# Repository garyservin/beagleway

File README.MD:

beagleway
=========

Plataforma robótica móvil basada en el principio del péndulo invertido utilizando una BeagleBone Black y un microcontrolador Mbed

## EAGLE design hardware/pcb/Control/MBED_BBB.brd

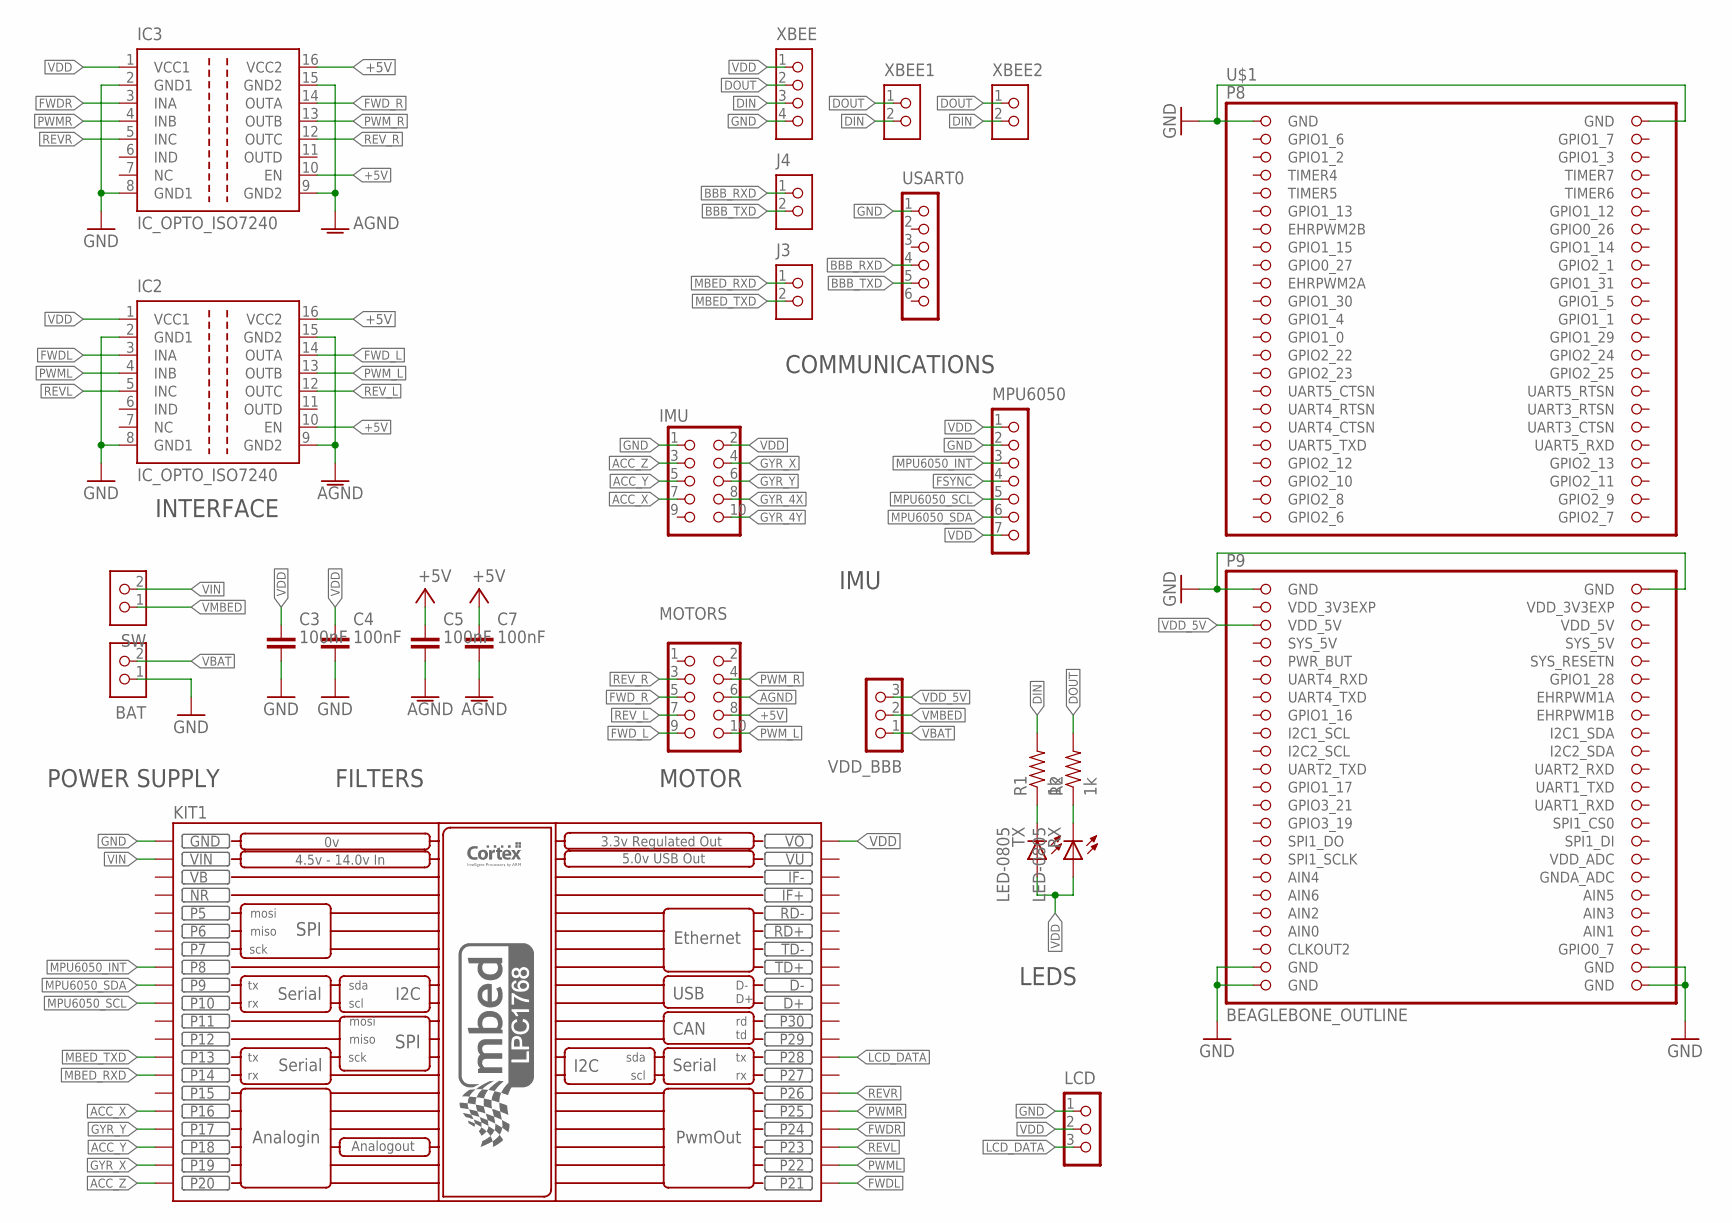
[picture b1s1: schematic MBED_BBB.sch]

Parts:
BAT: CON_HEADER_1X02-PTH-M; M1X02_M
C3, C4, C5, C7: 100nF; C0603
IC2, IC3: IC_OPTO_ISO7240; SOIC-16DW
IMU: CON_HEADER_2X05-PTH+SHROUDED_A; PINSHRD_PTH_2X05
J3, J4: CON_HEADER_1X02-PTH-M; M1X02_M
KIT1: MBED-SOCKET
LCD: CON_HEADER_1X03-PTH_M; M1X03_M
MOTORS: CON_HEADER_2X05-PTH+SHROUDED_A; PINSHRD_PTH_2X05
MPU6050: CON_HEADER_1X07-PTH_M; M1X07_M
R1, R2: 1k; R0603
RX: LED-0805
SW: CON_HEADER_1X02-PTH-POLAR; M1X02_P
TX: LED-0805
U$1: BEAGLEBONE_OUTLINE; BEAGLEBONE_SHIELD
USART0: CON_HEADER_1X06-PTH_M; M1X06_M
VDD_BBB: CON_HEADER_1X03-PTH_M; M1X03_M
XBEE: CON_HEADER_1X04-PTH_M; M1X04_M
XBEE1, XBEE2: CON_HEADER_1X02-PTH-M; M1X02_M

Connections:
+5V: C5.1, C7.1, IC2.10 (EN), IC2.16 (VCC2), IC3.10 (EN), IC3.16 (VCC2), MOTORS.8
ACC_X: IMU.7, KIT1.P16
ACC_Y: IMU.5, KIT1.P18
ACC_Z: IMU.3, KIT1.P20
AGND: C5.2, C7.2, IC2.9 (GND2), IC2.15 (GND2), IC3.9 (GND2), IC3.15 (GND2), MOTORS.6
AIN0: U$1.85 (AIN0)
BBB_RXD: J4.1, USART0.4
BBB_TXD: J4.2, USART0.5
DIN: R1.2, XBEE.3, XBEE1.2, XBEE2.2
DOUT: R2.2, XBEE.2, XBEE1.1, XBEE2.1
FSYNC: MPU6050.4
FWDL: IC2.3 (INA), KIT1.P21
FWDR: IC3.3 (INA), KIT1.P24
FWD_L: IC2.14 (OUTA), MOTORS.9
FWD_R: IC3.14 (OUTA), MOTORS.5
GND: BAT.1, C3.2, C4.2, IC2.2 (GND1), IC2.8 (GND1), IC3.2 (GND1), IC3.8 (GND1), IMU.1, KIT1.GND, LCD.1, MPU6050.2, U$1.1 (GND), U$1.2 (GND), U$1.47 (GND), U$1.48 (GND), U$1.89 (GND), U$1.90 (GND), U$1.91 (GND), U$1.92 (GND), USART0.1, XBEE.4
GYR_4X: IMU.8
GYR_4Y: IMU.10
GYR_X: IMU.4, KIT1.P19
GYR_Y: IMU.6, KIT1.P17
LCD_DATA: KIT1.P28, LCD.3
MBED_RXD: J3.1, KIT1.P14
MBED_TXD: J3.2, KIT1.P13
MPU6050_INT: KIT1.P8, MPU6050.3
MPU6050_SCL: KIT1.P10, MPU6050.5
MPU6050_SDA: KIT1.P9, MPU6050.6
NR: KIT1.NR
PWML: IC2.4 (INB), KIT1.P22
PWMR: IC3.4 (INB), KIT1.P25
PWM_L: IC2.13 (OUTB), MOTORS.10
PWM_R: IC3.13 (OUTB), MOTORS.4
REVL: IC2.5 (INC), KIT1.P23
REVR: IC3.5 (INC), KIT1.P26
REV_L: IC2.12 (OUTC), MOTORS.7
REV_R: IC3.12 (OUTC), MOTORS.3
RX_LED: R2.1, RX.C
SYS_5V: U$1.53 (SYS_5V)
TX_LED: R1.1, TX.C
VB: KIT1.VB
VBAT: BAT.2, VDD_BBB.1
VDD: C3.1, C4.1, IC2.1 (VCC1), IC3.1 (VCC1), IMU.2, KIT1.VOUT (VO), LCD.2, MPU6050.1, MPU6050.7, RX.A, TX.A, XBEE.1
VDD_3V3EXP: U$1.49 (VDD_3V3EXP), U$1.50 (VDD_3V3EXP)
VDD_5V: U$1.51 (VDD_5V), U$1.52 (VDD_5V), VDD_BBB.3
VIN: KIT1.VIN, SW.2
VMBED: SW.1, VDD_BBB.2
VU: KIT1.VU

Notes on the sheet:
POWER SUPPLY
COMMUNICATIONS
INTERFACE
FILTERS
LEDS
IMU
MOTOR

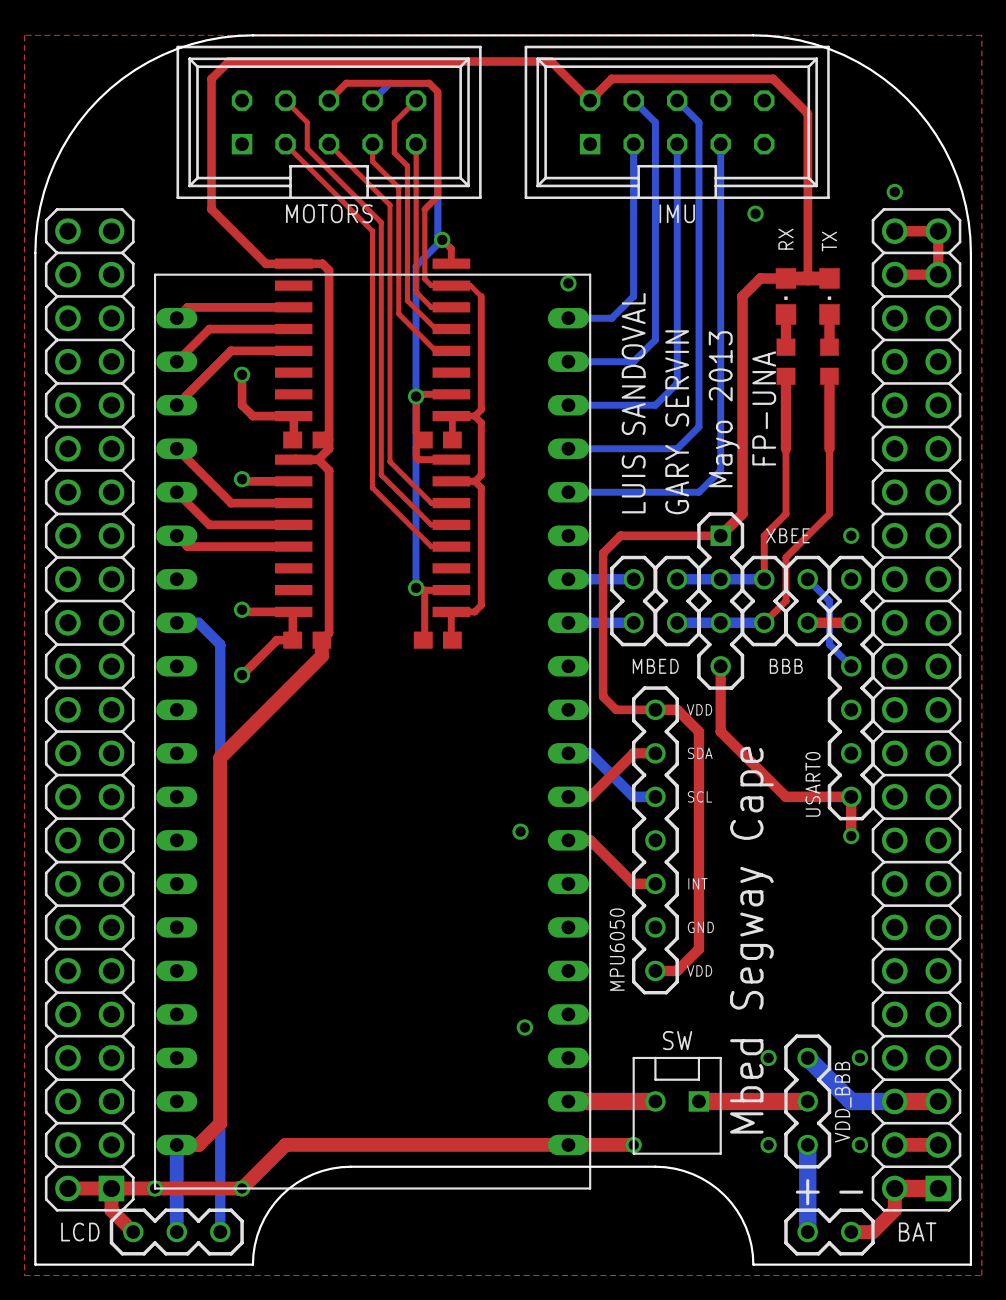
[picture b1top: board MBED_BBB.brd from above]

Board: 2 copper layers, 54.6 x 71.8 mm, 25 parts (0 on the bottom side), 38 nets.

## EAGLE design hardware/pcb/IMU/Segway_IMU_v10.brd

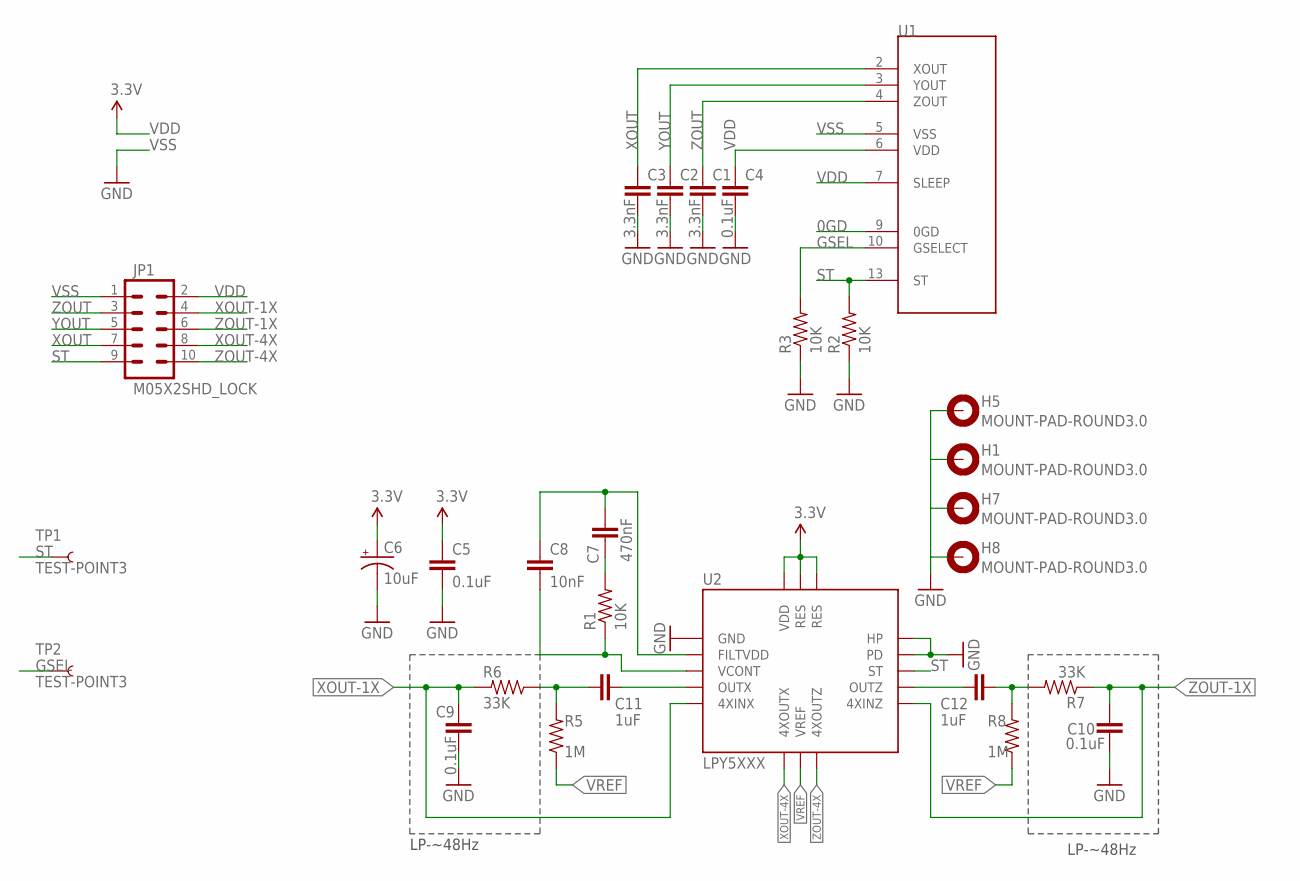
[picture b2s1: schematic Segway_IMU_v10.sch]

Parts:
C1, C2, C3: 3.3nF; 0402-CAP
C4, C5, C9, C10: 0.1uF; 0402-CAP
C6: 10uF; EIA3216
C7: 470nF; 0402-CAP
C8: 10nF; 0402-CAP
C11, C12: 1uF; 0402
H1, H5, H7, H8: MOUNT-PAD-ROUND3.0; 3,0-PAD
JP1: M05X2SHD_LOCK; 2X5-SHROUDED_LOCK
R1, R2, R3: 10K; 0402-RES
R5, R8: 1M; 0402-RES
R6, R7: 33K; 0402-RES
TP1, TP2: TEST-POINT3; PAD.03X.03
U1: MMA7361; LGA14
U2: LPY5XXX; ST-GYRO

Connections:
0GD: U1.9 (0GD)
F1: C7.1, C8.1, U2.2 (FILTVDD)
F2: C8.2, R1.1, U2.3 (VCONT)
GSEL: R3.2, TP2.P$1, U1.10 (GSELECT)
unnamed: C11.2, U2.4 (OUTX)
unnamed: C11.1, R5.2, R6.1
unnamed: C7.2, R1.2
unnamed: C12.1, U2.10 (OUTZ)
unnamed: C12.2, R7.2, R8.2
ST: JP1.9, R2.2, TP1.P$1, U1.13 (ST), U2.11 (ST)
VDD: C4.1, C5.1, C6.A (+), JP1.2, U1.6 (VDD), U1.7 (SLEEP), U2.14 (RES), U2.15 (RES), U2.16 (VDD)
VREF: R5.1, R8.1, U2.7 (VREF)
VSS: C1.2, C2.2, C3.2, C4.2, C5.2, C6.C (-), C9.1, C10.1, H1.B3,0, H5.B3,0, H7.B3,0, H8.B3,0, JP1.1, R2.1, R3.1, U1.5 (VSS), U2.1 (GND), U2.12 (PD), U2.13 (HP)
XOUT: C3.1, JP1.7, U1.2 (XOUT)
XOUT-1X: C9.2, JP1.4, R6.2, U2.5 (4XINX)
XOUT-4X: JP1.8, U2.6 (4XOUTX)
YOUT: C2.1, JP1.5, U1.3 (YOUT)
ZOUT: C1.1, JP1.3, U1.4 (ZOUT)
ZOUT-1X: JP1.6, R7.1, U2.9 (4XINZ)
ZOUT-4X: JP1.10, U2.8 (4XOUTZ)

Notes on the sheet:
LP-~48Hz

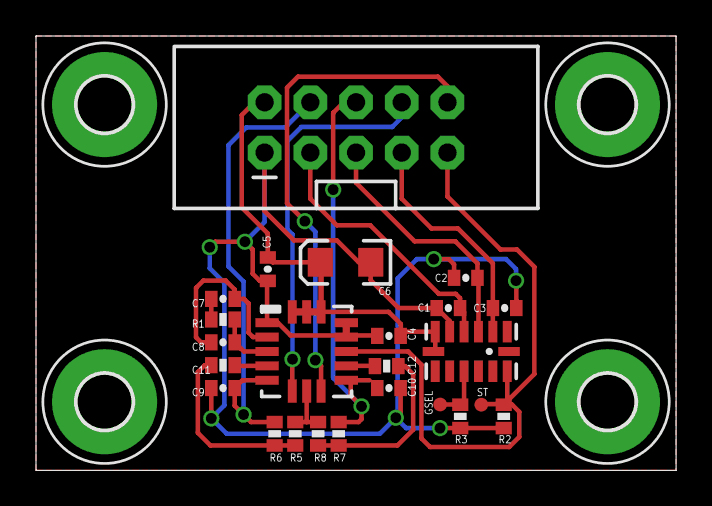
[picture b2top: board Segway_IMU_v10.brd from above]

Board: 2 copper layers, 35.6 x 24.1 mm, 28 parts (0 on the bottom side), 19 nets.

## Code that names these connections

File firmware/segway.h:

#ifndef SEGWAY_H
#define SEGWAY_H

#include "mbed.h"
#include "Motor.h"      // Library for the motor class
#include "PID.h"
//#include "matrix/Matrix.h"

#include <math.h>

// Mbed Pin Definitions

// Motors
// Left Motor
#define FWD_L   p21
#define PWM_L   p22
#define REV_L   p23
// Right Motor
#define FWD_R   p24
#define PWM_R   p25
#define REV_R   p26

// IMU
// Accelerometer
#define ACC_X   p16
#define ACC_Y   p18
#define ACC_Z   p20
// Gyroscope
// 1X
#define GYR_X   p19
#define GYR_Z   p17
// 4X - NOT USED @ THE MOMENT
//#define GYR_4X   p20
//#define GYR_4Y   p20

// Bluetooth
#define BT_TX   p13
#define BT_RX   p14

// Serial LCD
#define LCD_TX   p28
#define LCD_RX   p27

// PID
#define RATE	0.01

#define PI 3.14159265358979
#define TODEG 57.29577951

#define START	0
#define STOP	1
#define PAUSE	2
#define RUN	3
#define CAL	4

#define TRUE	1
#define FALSE	0

// Objects Declaration

// LEDs
//DigitalOut led1 ( LED1 );
//DigitalOut led2 ( LED2 );
//DigitalOut led3 ( LED3 );
//DigitalOut led4 ( LED4 );
//DigitalOut probe ( p5 );

//PwmOut led1 ( LED1 );
//PwmOut led2 ( LED2 );
//PwmOut led3 ( LED3 );

// IMU
AnalogIn accelerometerX ( ACC_X );
AnalogIn accelerometerY ( ACC_Y );
AnalogIn accelerometerZ ( ACC_Z );
AnalogIn gyroscopeX ( GYR_X );
AnalogIn gyroscopeZ ( GYR_Z );

// Serial Communications
Serial pc ( USBTX, USBRX );	// Serial Comm to PC
Serial bt ( BT_TX, BT_RX );	// Serial Comm to PC/Control via Bluetooth
Serial lcd ( LCD_TX, LCD_RX );	// Serial Comm to Serial LCD on top

//Motors
Motor LeftMotor ( PWM_L, FWD_L, REV_L ); // Left Motor
Motor RightMotor ( PWM_R, FWD_R, REV_R ); // Right Motor

// Timers
Timer t;
Timer master;
Timer period;

// Global Variables
double acc_scale = 0.8; // Accelerometer scale is 800 mV/g
double gyr_scale = 0.0005; // Gyroscope scale is 0.5 mV/dps (1x OUT)

double accy_offset = 0.5;
double gyrx_offset = 0.372727;

double acc_y = 0.0;
double gyr_x = 0.0;

double Ts = 0.0;

double lastError;
double iTerm;

double Kc = 50.0;
double Ti = 0.5;
double Td = 0.0;


// LTI Controller
//Matrix controllerGain(1,3);
//Matrix systemOutput(3,1);
//Matrix controlSignal(3,1);      // Control signal -  in our case u = -Ky as x = y
//double u = 0.0;     // Control signal -  in our case u = -Ky as x = y

// PID Controller
PID controller(Kc, Ti, Td, RATE); //Kc, Ti, Td, RATE

// Kalman filter variables and constants
const float Q_angle = 0.001; // Process noise covariance for the accelerometer - Sw
const float Q_gyro = 0.003; // Process noise covariance for the gyro - Sw
const float R_angle = 0.03; // Measurement noise covariance - Sv

double bias = 0;
double P_00 = 0, P_01 = 0, P_10 = 0, P_11 = 0;
double y, S;
double K_0, K_1;

double loop_time = 0.0;
double angle_kalman = 0.0;
double angleCompl = 0.0;
float master_timer = 0.0;

double acc_angle = 0.0;
double gyr_rad = 0.0;
double angle = 0.0;

double targetAngle = 0.0;
double output = 0.0;

// Function Prorotypes
void InitSegway ( void );
void CalibrateSensors ( void );
void ReadSensors ( void );
void GetAngle(void);
void SetOutput(void);
void InitPID(void);
void InitMotors(void);
void InitOffsets(void);
void PrintHeader(void);
void Timers (int action);

double kalman(double newAngle, double newRate, double dtime);

void RxData(void);
void processing(void);

#endif

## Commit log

2014-02-16 Add svg file for mechanical base
